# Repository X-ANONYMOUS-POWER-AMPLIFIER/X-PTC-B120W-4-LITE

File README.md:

# X-PTC-B120W-4-LITE PROTECTION CIRCUIT FOR X-B120W-4-LITE CLASS-B POWER AMPLIFIER MAIN-CIRCUIT

X-PTC-B120W-4-LITE is a protection circuit module for [X-B120W-4-LITE CLASS-B POWER AMPLIFIER MAIN-CIRCUIT](https://github.com/X-ANONYMOUS-POWER-AMPLIFIER/X-B120W-4-LITE/). It provides both open-circuit and short-circuit protection for protecting both side of the power amplifier main-circuit and the loudspeaker. This circuit is designed to be fit on a small size single-sided PCB and for easy to install.

This X-PTC-B120W-4-LITE is designed to work in 12V DC non-symmetrical operating voltage. None of additional operating voltage is needed. The [X-10A42V-DDSB-PSU PSU module](https://github.com/X-ANONYMOUS-POWER-AMPLIFIER/X-10A42V-DDSB-PSU) is applicable to provide operating voltages for powering-up both [X-B120W-4-LITE CLASS-B POWER AMPLIFIER MAIN-CIRCUIT](https://github.com/X-ANONYMOUS-POWER-AMPLIFIER/X-B120W-4-LITE/) module and this X-PTC-B120W-4-LITE protection module. 

## License

1. **License Grant**  
The Licensor hereby grants you a worldwide, royalty-free, non-exclusive, perpetual license to use the circuit design for the non-commercial purposes only.
2. **Conditions**  
Attribution: You must provide credit to the original creator when distributing this circuit design.
3. **Disclaimer of Warranty**  
THE DESIGN IS PROVIDED "AS IS". THE LICENSOR MAKES NO WARRANTIES, EXPRESS OR IMPLIED, REGARDING THE DESIGN, INCLUDING BUT NOT LIMITED TO ANY IMPLIED WARRANTIES OF MERCHANTABILITY OR FITNESS FOR A PARTICULAR PURPOSE.
4. **Limitation of Liability**  
IN NO EVENT SHALL THE LICENSOR BE LIABLE FOR ANY DAMAGES, INCLUDING BUT NOT LIMITED TO DIRECT, INDIRECT, INCIDENTAL, OR CONSEQUENTIAL DAMAGES ARISING OUT OF THE USE OF THE DESIGN.

# Design Files Bundle Download

Design files bundle is available for download by follow the URL: [https://github.com/X-ANONYMOUS-POWER-AMPLIFIER/X-PTC-B120W-4-LITE/archive/refs/heads/main.zip](https://github.com/X-ANONYMOUS-POWER-AMPLIFIER/X-PTC-B120W-4-LITE/archive/refs/heads/main.zip)

The main design files of schematic and PCB design are in [KiCad](https://www.kicad.org/) V.9.x format.

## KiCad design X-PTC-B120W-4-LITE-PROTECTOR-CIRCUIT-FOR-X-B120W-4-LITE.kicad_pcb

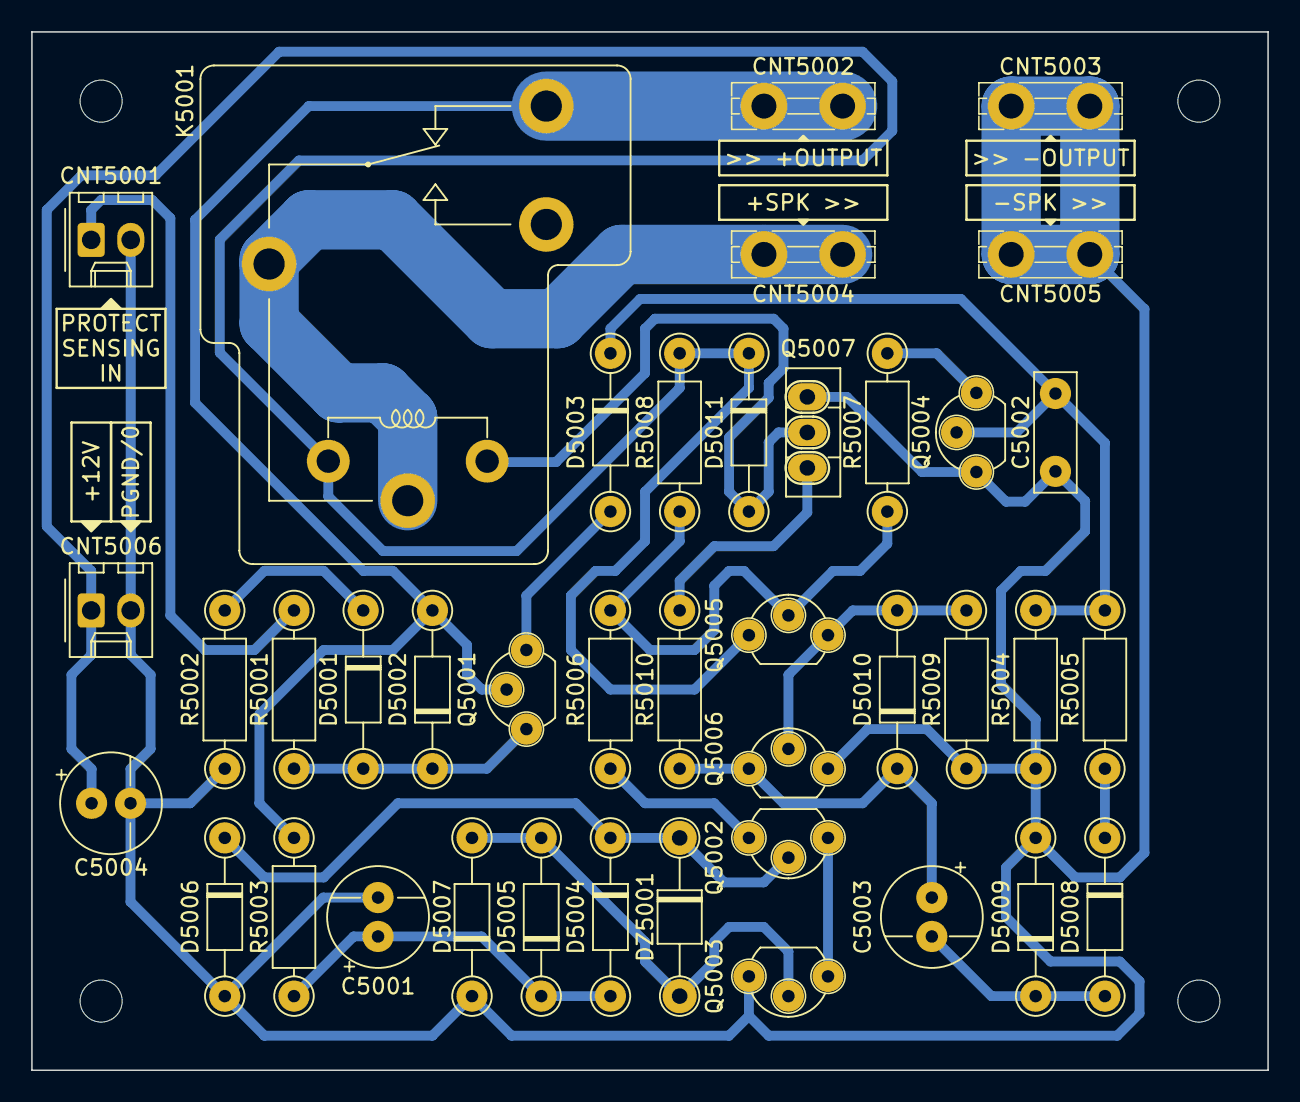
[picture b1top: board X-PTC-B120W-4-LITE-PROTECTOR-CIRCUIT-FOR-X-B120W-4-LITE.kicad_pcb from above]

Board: 2 copper layers, 79.4 x 66.7 mm, 40 parts (0 on the bottom side), 22 nets.

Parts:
C5001, C5003: 33uF; CP_Radial_D6.3mm_P2.50mm
C5002: 0.1uF; C_Rect_L7.5mm_W2.5mm_P5.00mm_WIMA_MKS2
C5004: 47uF; CP_Radial_D6.3mm_P2.50mm
CNT5001, CNT5006: 22-27-2021; Molex_KK-254_AE-6410-02A_1x02_P2.54mm_Vertical
CNT5002, CNT5003, CNT5004, CNT5005: 2376582-2; PCB_TAB_250_FASTON_TPBR
D5001, D5002, D5003, D5004, D5005, D5006, D5007, D5008, D5009, D5010, D5011: 1N4148; D_DO-35_SOD27_P10.16mm_Horizontal
DZ5001: 1N4730; D_T-1_P10.16mm_Horizontal
K5001: Relay_SPDT_RAYEX-L90
Q5001, Q5003, Q5005, Q5006: 2N5401; TO-92_3_Wide
Q5002, Q5004: 2N5551; TO-92_3_Wide
Q5007: BD139; TO-126-3_Vertical
R5001, R5010: 5.6K; R_Axial_DIN0207_L6.3mm_D2.5mm_P10.16mm
R5002, R5003: 47K; R_Axial_DIN0207_L6.3mm_D2.5mm_P10.16mm
R5004: 51K; R_Axial_DIN0207_L6.3mm_D2.5mm_P10.16mm
R5005: 39K; R_Axial_DIN0207_L6.3mm_D2.5mm_P10.16mm
R5006, R5007, R5009: 12K; R_Axial_DIN0207_L6.3mm_D2.5mm_P10.16mm
R5008: 8.2K; R_Axial_DIN0207_L6.3mm_D2.5mm_P10.16mm

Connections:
0: C5001.2, C5002.2, C5004.2, CNT5001.2, CNT5003.1, CNT5005.1, CNT5006.2, D5006.2 (A), D5007.1 (K), D5009.2 (A), Q5003.3 (C), Q5004.1 (E), Q5006.3 (C), Q5007.1 (E), R5002.2, R5004.2, R5009.2
+12V: C5004.1, CNT5006.1, D5011.1 (K), K5001.2, Q5005.1 (E), R5008.1
LSO: CNT5001.1, R5001.2
unnamed: D5001.2 (A), D5002.1 (K), Q5001.1 (E), R5001.1
unnamed: D5001.1 (K), R5002.1
unnamed: D5003.2 (A), Q5001.3 (C)
unnamed: C5002.1, D5003.1 (K), Q5004.2 (B), R5004.1, R5005.2
unnamed: C5001.1, D5004.2 (A), D5005.1 (K), R5003.1
unnamed: D5004.1 (K), D5006.1 (K), DZ5001.1 (K), Q5002.2 (B)
unnamed: D5005.2 (A), D5007.2 (A), DZ5001.2 (A), Q5003.2 (B)
unnamed: C5003.2, D5008.2 (A), D5009.1 (K)
unnamed: D5008.1 (K), R5005.1
unnamed: D5010.2 (A), Q5005.3 (C), Q5006.2 (B), R5009.1
unnamed: C5003.1, D5010.1 (K), Q5006.1 (E), R5010.2
unnamed: D5011.2 (A), K5001.5, Q5007.2 (C)
unnamed: Q5002.3 (C), R5006.2
unnamed: Q5002.1 (E), Q5003.1 (E)
unnamed: Q5004.3 (C), R5007.2
unnamed: Q5005.2 (B), R5006.1, R5007.1, R5008.2
unnamed: Q5007.3 (B), R5010.1
OUTPUT: CNT5002.1, D5002.2 (A), K5001.4, Q5001.2 (B), R5003.2
SPK: CNT5004.1, K5001.1

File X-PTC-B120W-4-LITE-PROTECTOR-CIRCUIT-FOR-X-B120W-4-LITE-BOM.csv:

"Reference","Value","Rating","Description","MFR Number","Manufacturer","Qty"
"C5001,C5003","33uF","16V","Aluminum Electrolytic Capacitors - Radial Leaded 33uF 16V","ECE-A1CKA330","Panasonic","2"
"C5002","0.1uF","63V DC","Film Capacitors 0.1 uF 63 VDC 5%","MKS2C031001A00JI00","WIMA","1"
"C5004","47uF","16V","Aluminum Electrolytic Capacitors - Radial Leaded 47uF 16V","ECE-A1CKA470","Panasonic","1"
"CNT5001,CNT5006","22-27-2021","","Headers & Wire Housings 2 POS HEADER","22-27-2021","Molex","2"
"CNT5002,CNT5003,CNT5004,CNT5005","2376582-2","","250 FASTON PCB TAB TPBR","2376582-2","TE Connectivity","4"
"D5001,D5002,D5003,D5004,D5005,D5006,D5007,D5008,D5009,D5010,D5011","1N4148","","Small Signal Switching Diodes Small Signal Diode, DO-35, 100V, 0.2A, 175C","1N4148","Diotec Semiconductor","11"
"DZ5001","1N4730","","Zener Diodes 3.9 Volt 1.3 Watt","1N4730A-TAP","Vishay Semiconductors","1"
"K5001","SLA-12VDC-SL-C","","SUBMINATURE HIGH POWER RELAY 5P","SLA-12VDC-SL-C","Songle Relay","1"
"Q5001,Q5003,Q5005,Q5006","2N5401","","Bipolar Transistors - BJT PNP 160Vcbo 150Vceo 5.0Vebo 600mA 625mW","2N5401 TIN/LEAD","Central Semiconductor ","4"
"Q5002,Q5004","2N5551","","Bipolar Transistors - BJT NPN 180Vcbo 160Vceo 6.0Vebo 600mA 625mW\","2N5551 TIN/LEAD","Central Semiconductor ","2"
"Q5007","BD139G","","Bipolar Transistors - BJT 1.5A 80V 12.5W NPN","BD139G","onsemi","1"
"R5001,R5010","5.6K","0.25W","Metal Film Resistors - Through Hole 5.6K OHM 1/4W 1%","MFR-25FRE52-5K6","YAGEO","2"
"R5002,R5003","47K","0.25W","Metal Film Resistors - Through Hole 47K OHM 1/4W 1%","MFR-25FRE52-47K","YAGEO","2"
"R5004","51K","0.25W","Metal Film Resistors - Through Hole 510 OHM 1/4W 1%","MFR-25FRE52-51K","YAGEO","1"
"R5005","39K","0.25W","Metal Film Resistors - Through Hole 39K OHM 1/4W 1%","MFR-25FRE52-39K","YAGEO","1"
"R5006,R5007,R5009","12K","0.25W","Metal Film Resistors - Through Hole 12K OHM 1/4W 1%","MFR-25FRE52-12K","YAGEO","3"
"R5008","8.2K","0.25W","Metal Film Resistors - Through Hole 8.2K OHM 1/4W 1%","MFR-25FRE52-8K2","YAGEO","1"
